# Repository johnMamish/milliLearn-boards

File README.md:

# milliLearn-boards
Dev boards targeting low-power machine learning

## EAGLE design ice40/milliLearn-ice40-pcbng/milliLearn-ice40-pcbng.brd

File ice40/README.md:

#### milliLearn iCE40

milliLearn/iCE40 is an FPGA dev board focused at ultra low-power machine learning research. As a platform itself, it's not meant to be deployed, but is instead meant for benchtop power and performance metering.

The files in the pcb-ng directory are a smaller version of the board that might be less convenient to work with - it saves space at the expense of having limited header pins and no swappable memory modules.

Circuit checklist:
 - [x] 3.3v, 1.8v linear regulators
 - [x] USB port
 - [x] Selectable Vddios
 - [x] FT232H for programming configuration flash
 - [x] iCE40 FPGA
 - [x] configuration flash
 - [x] uart connection from iCE40
 - [x] Connector for [Sparkfun-produced hm01b0 image sensor](https://www.sparkfun.com/products/15570)
 - [x] Modular memory footprints
   - [x] 0.1" header modular pins
      - [x] Swap modules easily
      - [x] Program modules easily
   - [x] 4 spaces for memory chips in total (excluding configuration flash)
   - [x] Choose between the follwing parts, which are all footprint compatible
      - [x] SPI FRAM
      - [x] QSPI Flash
      - [ ] SRAM
 - [x] Current sense amps with header pins for monitoring output voltage
 - [x] Seperate power consumption monitoring for
   - [x] Each memory chip
   - [x] Each sensor
   - [x] FPGA
      - [x] Vddcore + Vddpll
      - [x] Vccio{0, 1, 2}
 - [x] i2s microphone(s)   SPH0645LM4H-B
 - [x] Sparkfun qwiic connect compatible connector
 - [x] All i/os broken out for debug
 - [x] oscillator
 - [x] a couple LEDs, a couple buttons (could re-use config flash pins, hm01b0_int, hm01b0_trig, or ice40_gpio)

Future featues:
 - [ ] Onboard mcu for measuring power in firmware and reporting over UART

random notes:

###### Config memory read speed

When using iceprog, the config flash memory is written by the ft232hq at 6MHz.
The iCE40 starts by reading the config flash at about 12MHz. This is the default read frequency. There are options to put a "speed up the read" near the beginning of the bitstream (refer to Lattice Technical Note 1248: "iCE40 Programming and Configuration")

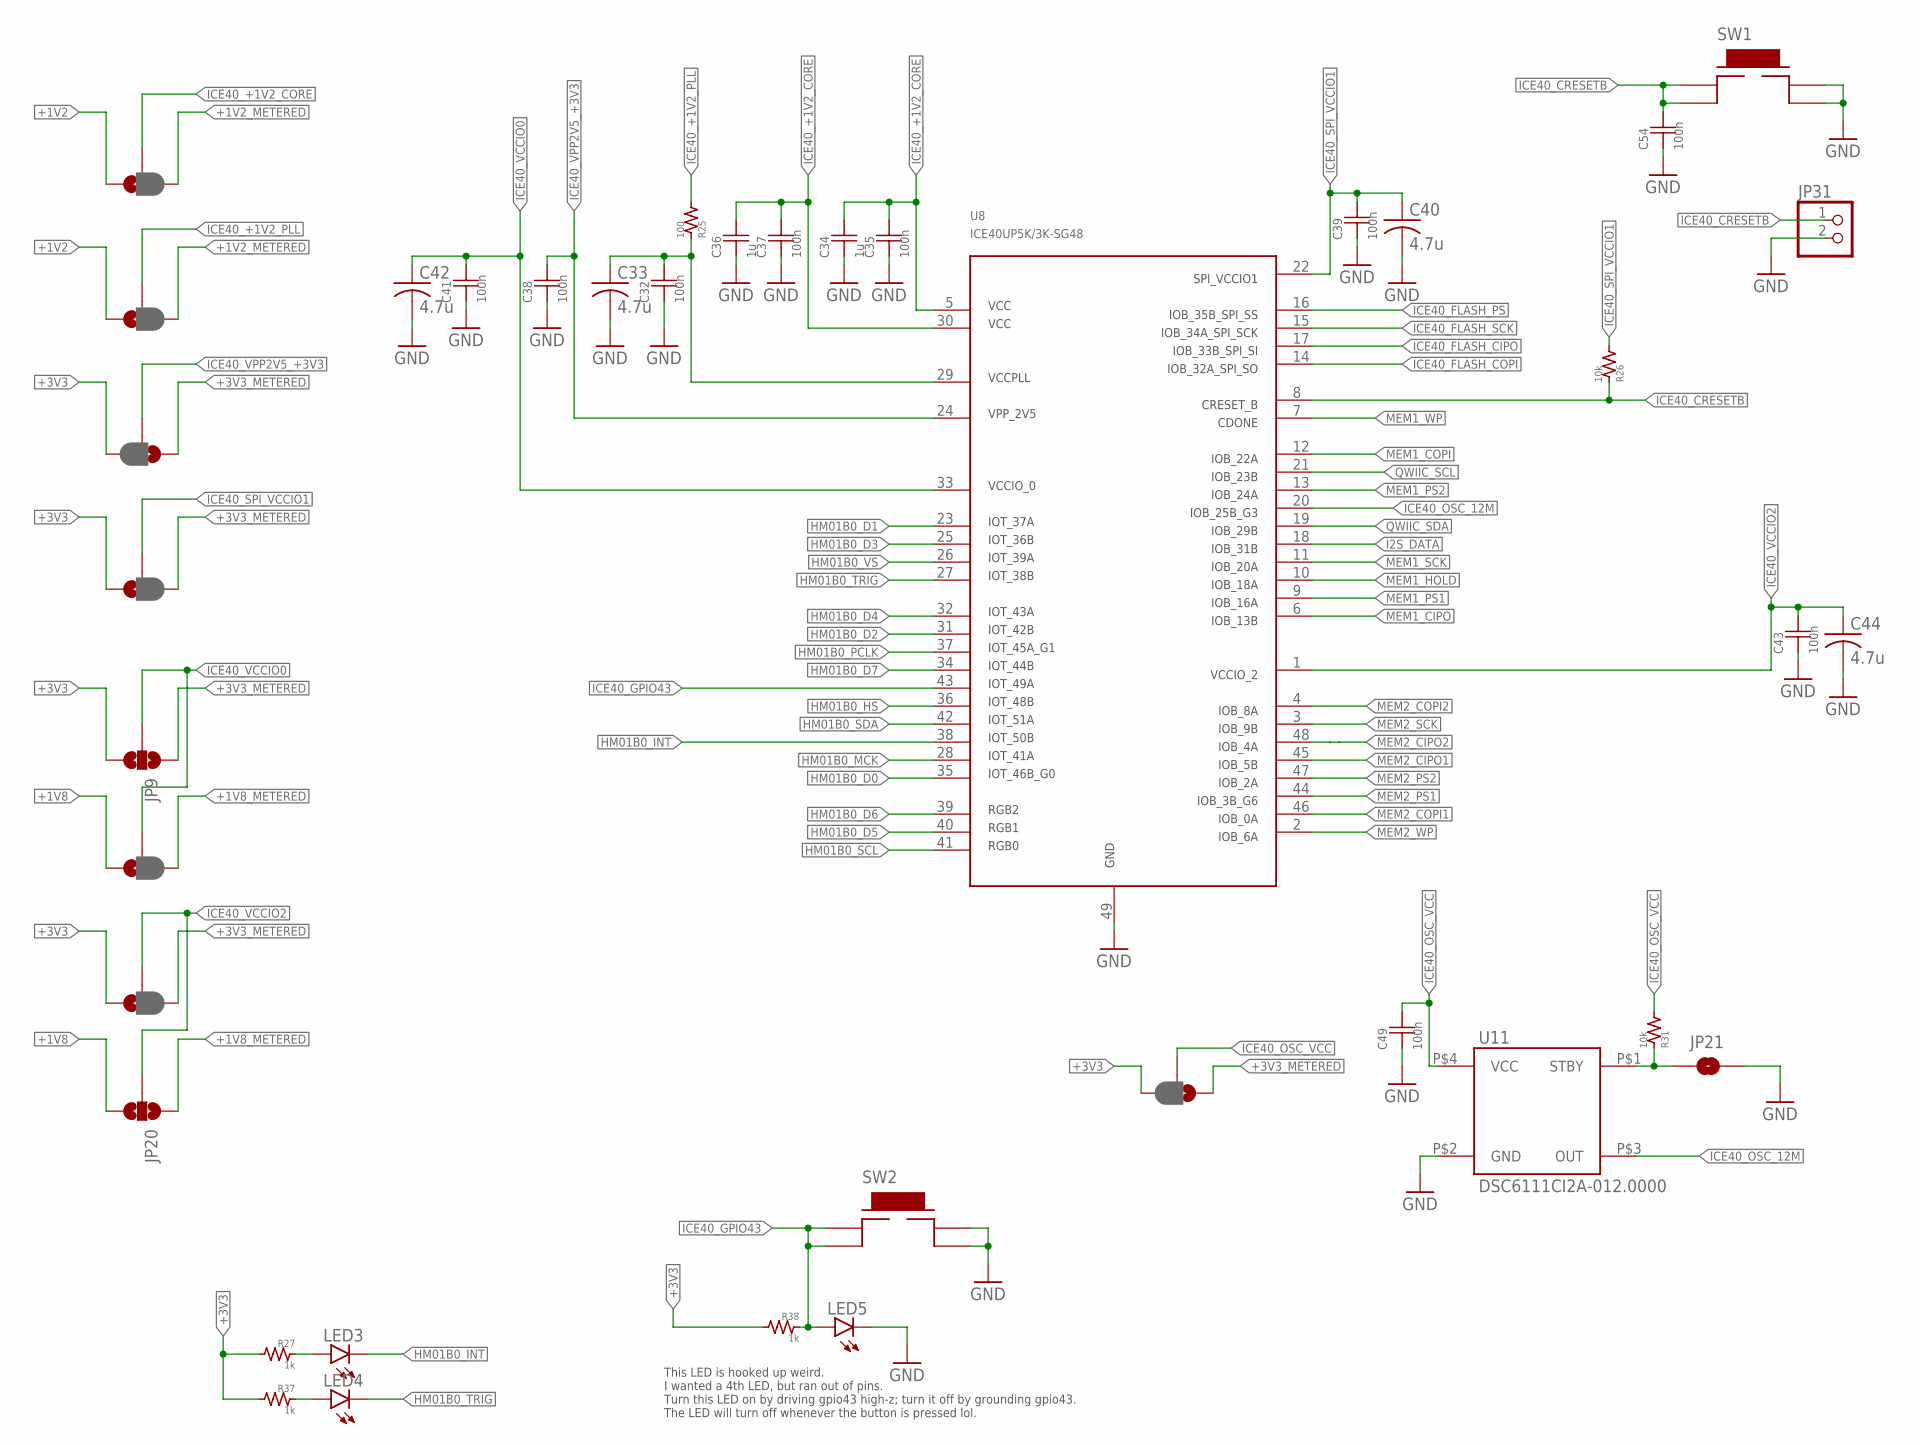
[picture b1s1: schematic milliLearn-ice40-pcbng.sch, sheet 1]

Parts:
C32, C35, C37, C38, C39, C41, C43, C49, C54: 100n; C0402_COMPACT; MFR_PN CL05B104KO5NNNC
C33, C40, C42, C44: 4.7u; C0603; MFR_PN CL10A475KA8NQNC
C34, C36: 1u; C0402_COMPACT; MFR_PN CL05A105KO5NNNC
JP5, JP6, JP7, JP8, JP13, JP14, JP19: JUMPER-SMT_3_1-NC_PASTE_NO-SILK; SMT-JUMPER_3_1-NC_PASTE_NO-SILK
JP9, JP20: JUMPER-SMT_3_NO_NO-SILK; SMT-JUMPER_3_NO_NO-SILK
JP21: JUMPER-SMT_2_NO_NO-SILK; SMT-JUMPER_2_NO_NO-SILK
JP31: PINHD-1X2; 1X02
LED3, LED4, LED5: LEDCHIPLED_0603; CHIPLED_0603; MFR_PN LTST-C191KRKT
R25: 100; R0402_COMPACT; MFR_PN RC0402FR-07100RL
R26, R31: 10k; R0402_COMPACT; MFR_PN ERJ-2RKF1002X
R27, R37, R38: 1k; R0402_COMPACT; MFR_PN ERJ-2RKF1001X
SW1, SW2: TE_FSMJSMA; MFR_PN FSM4JSMATR
U8: ICE40UP5K/3K-SG48; MFR_PN ICE40UP5K-SG48I
U11: DSC6111CI2A-012.0000; MFR_PN DSC6111CI2A-012.0000

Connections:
+1V2: JP5.1, JP6.1; also elsewhere on the board
+1V2_METERED: JP5.3, JP6.3; also elsewhere on the board
+1V8: JP13.1, JP20.3; also elsewhere on the board
+1V8_METERED: JP13.3, JP20.1; also elsewhere on the board
+3V3: JP7.3, JP8.1, JP9.3, JP14.1, JP19.3, R27.1, R37.1, R38.1; also elsewhere on the board
+3V3_METERED: JP7.1, JP8.3, JP9.1, JP14.3, JP19.1; also elsewhere on the board
GND: C32.1, C33.2, C34.1, C35.1, C36.1, C37.1, C38.1, C39.1, C40.2, C41.1, C42.2, C43.1, C44.2, C49.1, C54.1, JP21.2, JP31.2, LED5.C, SW1.P$3, SW1.P$4, SW2.P$3, SW2.P$4, U8.49, U11.P$2 (GND); also elsewhere on the board
HM01B0_D0: U8.35; also elsewhere on the board
HM01B0_D1: U8.23; also elsewhere on the board
HM01B0_D2: U8.31; also elsewhere on the board
HM01B0_D3: U8.25; also elsewhere on the board
HM01B0_D4: U8.32; also elsewhere on the board
HM01B0_D5: U8.40; also elsewhere on the board
HM01B0_D6: U8.39; also elsewhere on the board
HM01B0_D7: U8.34; also elsewhere on the board
HM01B0_HS: U8.36; also elsewhere on the board
HM01B0_INT: LED3.C, U8.38; also elsewhere on the board
HM01B0_MCK: U8.28; also elsewhere on the board
HM01B0_PCLK: U8.37; also elsewhere on the board
HM01B0_SCL: U8.41; also elsewhere on the board
HM01B0_SDA: U8.42; also elsewhere on the board
HM01B0_TRIG: LED4.C, U8.27; also elsewhere on the board
HM01B0_VS: U8.26; also elsewhere on the board
I2S_DATA: U8.18; also elsewhere on the board
ICE40_+1V2_CORE: C34.2, C35.2, C36.2, C37.2, JP5.2, U8.5, U8.30
ICE40_+1V2_PLL: JP6.2, R25.1
ICE40_CRESETB: C54.2, JP31.1, R26.2, SW1.P$1, SW1.P$2, U8.8; also elsewhere on the board
ICE40_FLASH_CIPO: U8.17; also elsewhere on the board
ICE40_FLASH_COPI: U8.14; also elsewhere on the board
ICE40_FLASH_PS: U8.16; also elsewhere on the board
ICE40_FLASH_SCK: U8.15; also elsewhere on the board
ICE40_GPIO43: LED5.A, R38.2, SW2.P$1, SW2.P$2, U8.43
ICE40_OSC_12M: U8.20, U11.P$3 (OUT); also elsewhere on the board
ICE40_OSC_VCC: C49.2, JP19.2, R31.1, U11.P$4 (VCC)
ICE40_SPI_VCCIO1: C39.2, C40.1, JP8.2, R26.1, U8.22
ICE40_VCCIO0: C41.2, C42.1, JP9.2, JP13.2, U8.33
ICE40_VCCIO2: C43.2, C44.1, JP14.2, JP20.2, U8.1
ICE40_VCCPLL: C32.2, C33.1, R25.2, U8.29
ICE40_VPP2V5_+3V3: C38.2, JP7.2, U8.24
MEM1_!HOLD: U8.10; also elsewhere on the board
MEM1_!WP: U8.7; also elsewhere on the board
MEM1_CIPO: U8.6; also elsewhere on the board
MEM1_COPI: U8.12; also elsewhere on the board
MEM1_PS1: U8.9; also elsewhere on the board
MEM1_PS2: U8.13; also elsewhere on the board
MEM1_SCK: U8.11; also elsewhere on the board
MEM2_!WP: U8.2; also elsewhere on the board
MEM2_CIPO1: U8.45; also elsewhere on the board
MEM2_CIPO2: U8.48; also elsewhere on the board
MEM2_COPI1: U8.46; also elsewhere on the board
MEM2_COPI2: U8.4; also elsewhere on the board
MEM2_PS1: U8.44; also elsewhere on the board
MEM2_PS2: U8.47; also elsewhere on the board
MEM2_SCK: U8.3; also elsewhere on the board
unnamed: JP21.1, R31.2, U11.P$1 (STBY)
unnamed: LED3.A, R27.2
unnamed: LED4.A, R37.2
QWIIC_SCL: U8.21; also elsewhere on the board
QWIIC_SDA: U8.19; also elsewhere on the board

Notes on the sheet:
This LED is hooked up weird. I wanted a 4th LED, but ran out of pins. Turn this LED on by driving gpio43 high-z; turn it off by grounding gpio43. The LED will turn off whenever the button is pressed lol.

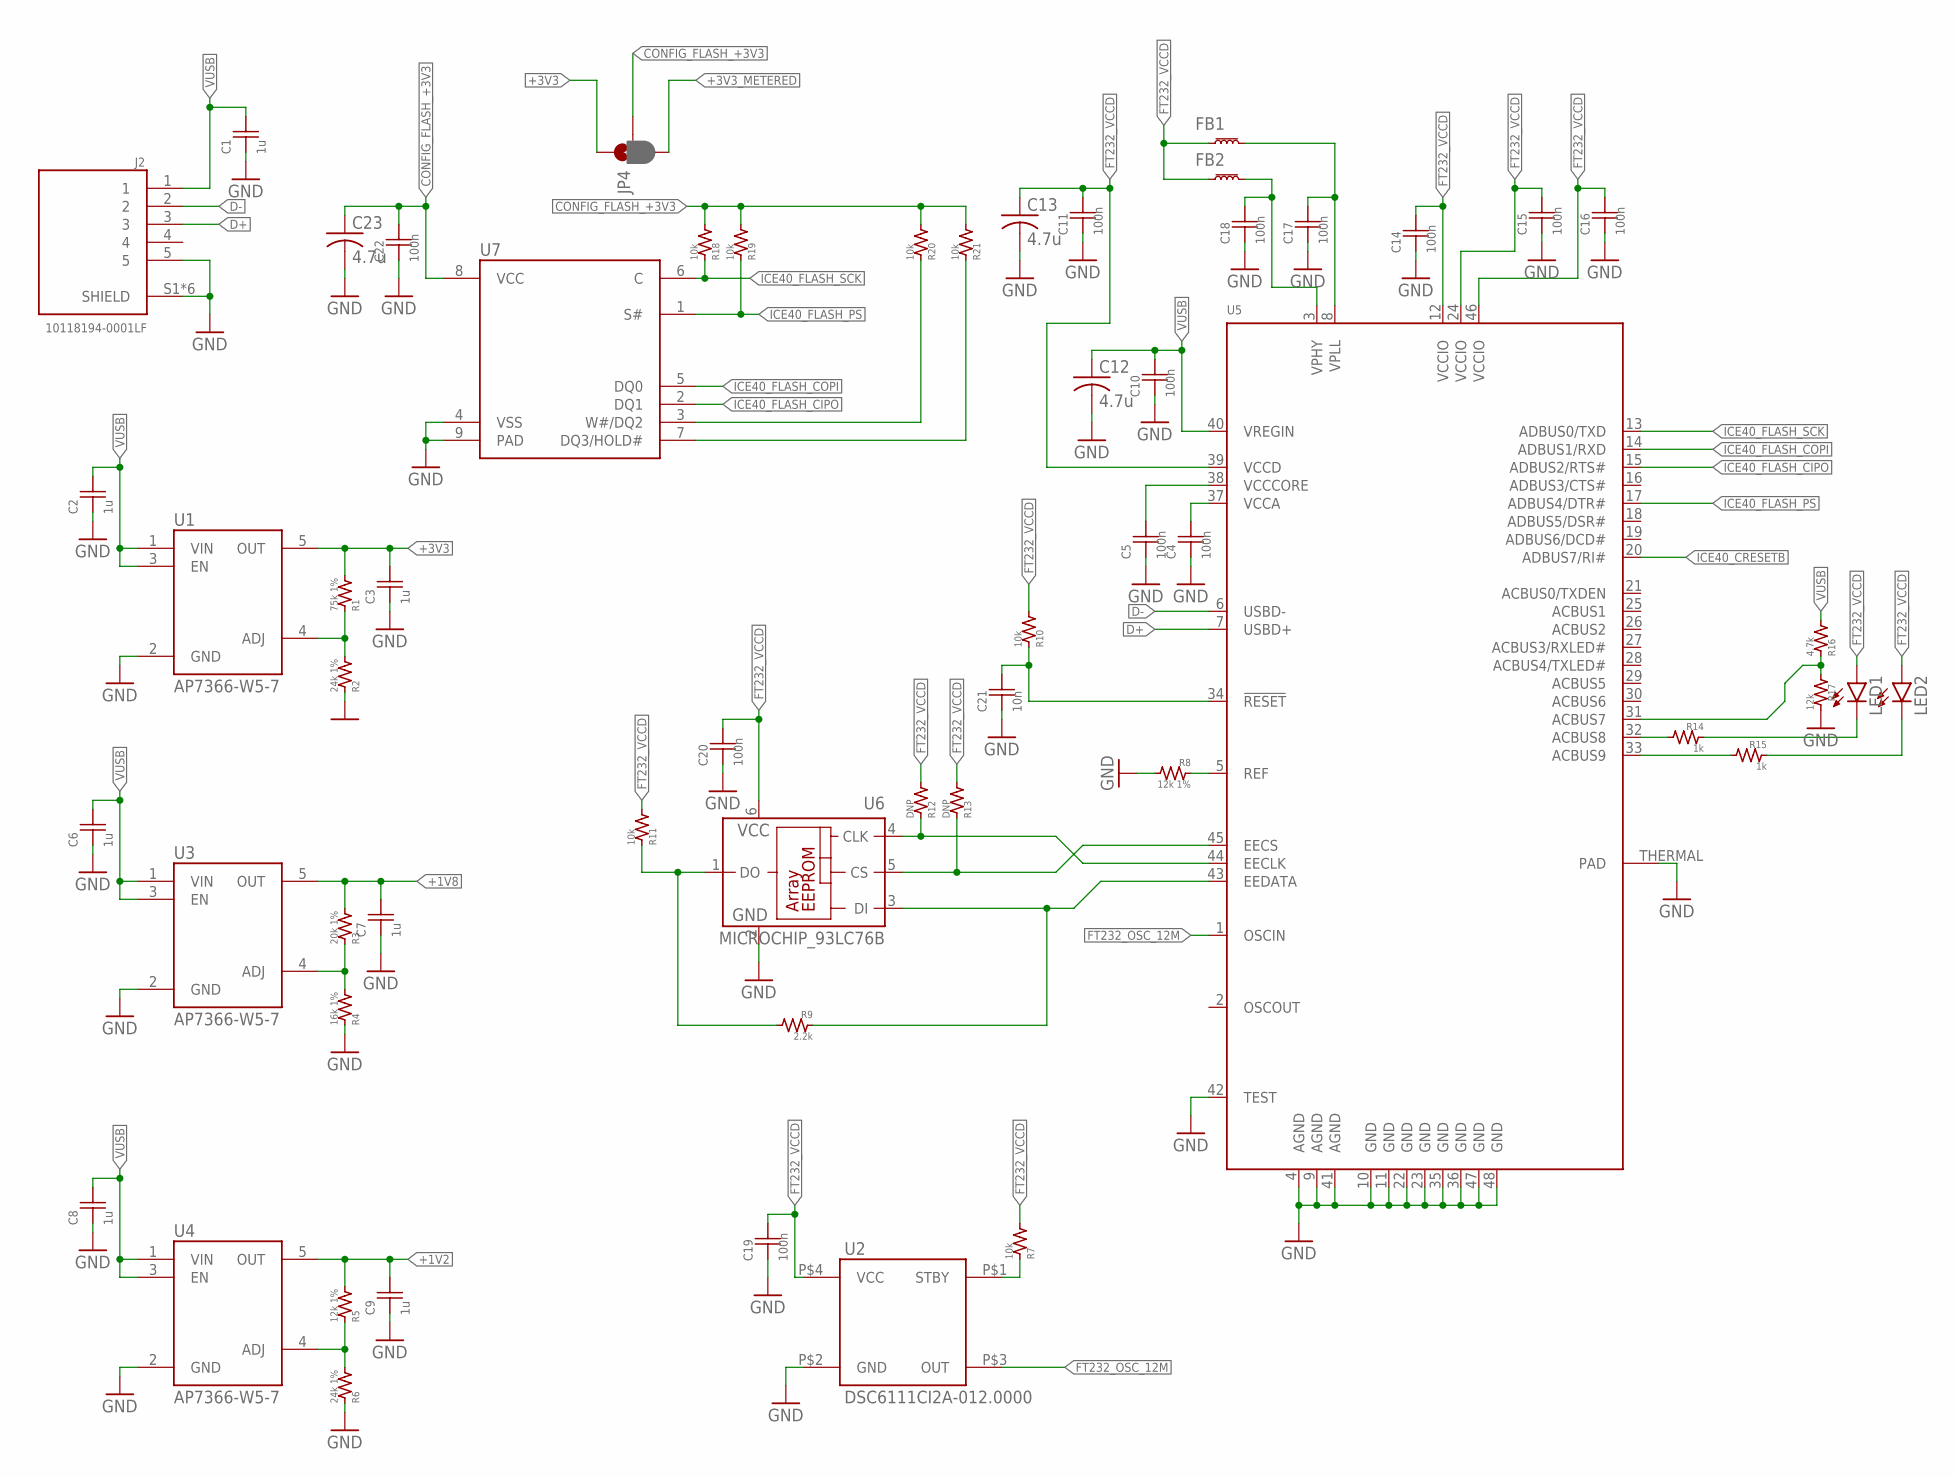
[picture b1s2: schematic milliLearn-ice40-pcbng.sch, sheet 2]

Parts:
C1, C2, C3, C6, C7, C8, C9: 1u; C0402_COMPACT; MFR_PN CL05A105KO5NNNC
C4, C5, C10, C11, C14, C15, C16, C17, C18, C19, C20, C22: 100n; C0402_COMPACT; MFR_PN CL05B104KO5NNNC
C12, C13, C23: 4.7u; C0603; MFR_PN CL10A475KA8NQNC
C21: 10n; C0402_COMPACT; MFR_PN CL05B103KO5NNNC
FB1, FB2: BLM18KG601SN1D
J2: 10118194-0001LF; AMPHENOL_10118194-0001LF; MFR_PN 10118194-0001LF
JP4: JUMPER-SMT_3_1-NC_PASTE_NO-SILK; SMT-JUMPER_3_1-NC_PASTE_NO-SILK
LED1, LED2: LEDCHIPLED_0603; CHIPLED_0603; MFR_PN LTST-C191KRKT
R1: 75k 1%; R0402_COMPACT; MFR_PN ERJ-2RKF7502X
R2, R6: 24k 1%; R0402_COMPACT; MFR_PN ERJ-2RKF2402X
R3: 20k 1%; R0402_COMPACT; MFR_PN ERJ-2RKF2002X
R4: 16k 1%; R0402_COMPACT; MFR_PN ERJ-2RKF1602X
R5, R8: 12k 1%; R0402_COMPACT; MFR_PN ERJ-2RKF1202X
R7, R10, R11, R18, R19, R20, R21: 10k; R0402_COMPACT; MFR_PN ERJ-2RKF1002X
R9: 2.2k; R0402_COMPACT; MFR_PN ERJ-2RKF2201X
R12, R13: DNP; R0402_COMPACT; MFR_PN ERJ-2RKF1002X
R14, R15: 1k; R0402_COMPACT; MFR_PN ERJ-2RKF1001X
R16: 4.7k; R0402_COMPACT; MFR_PN ERJ-2RKF4701X
R17: 12k; R0402_COMPACT; MFR_PN ERJ-2RKF1202X
U1, U3, U4: AP7366-W5-7
U2: DSC6111CI2A-012.0000; MFR_PN DSC6111CI2A-012.0000
U5: MICROBUILDER_FT232HQ; MICROBUILDER_QFN48_8MM; MFR_PN FT232HQ-REEL
U6: MICROCHIP_93LC76B; MICROCHIP_SOT23-6; MFR_PN 93LC56BT-I/OT
U7: MT25QL128ABA1EW7; MFR_PN MT25QL128ABA1EW7-0SIT

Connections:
+1V2: C9.2, R5.1, U4.5 (OUT); also elsewhere on the board
+1V8: C7.2, R3.1, U3.5 (OUT); also elsewhere on the board
+3V3: C3.2, JP4.1, R1.1, U1.5 (OUT); also elsewhere on the board
+3V3_METERED: JP4.3; also elsewhere on the board
CONFIG_FLASH_+3V3: C22.2, C23.1, JP4.2, R18.1, R19.1, R20.1, R21.1, U7.8 (VCC)
D+: J2.3, U5.7 (USBD+)
D-: J2.2, U5.6 (USBD-)
FT232_OSC_12M: U2.P$3 (OUT), U5.1 (OSCIN)
FT232_VCCD: C11.2, C13.1, C14.2, C15.2, C16.2, C19.2, C20.2, FB1.1, FB2.1, LED1.A, LED2.A, R7.1, R10.1, R11.1, R12.1, R13.1, U2.P$4 (VCC), U5.12 (VCCIO), U5.24 (VCCIO), U5.39 (VCCD), U5.46 (VCCIO), U6.6 (VCC)
GND: C1.1, C2.1, C3.1, C4.1, C5.1, C6.1, C7.1, C8.1, C9.1, C10.1, C11.1, C12.2, C13.2, C14.1, C15.1, C16.1, C17.1, C18.1, C19.1, C20.1, C21.1, C22.1, C23.2, J2.5, J2.S1 (SHIELD), J2.S2 (SHIELD), J2.S3 (SHIELD), J2.S4 (SHIELD), J2.S5 (SHIELD), J2.S6 (SHIELD), R2.2, R4.2, R6.2, R8.1, R17.2, U1.2 (GND), U2.P$2 (GND), U3.2 (GND), U4.2 (GND), U5.4 (AGND), U5.9 (AGND), U5.10 (GND), U5.11 (GND), U5.22 (GND), U5.23 (GND), U5.35 (GND), U5.36 (GND), U5.41 (AGND), U5.42 (TEST), U5.47 (GND), U5.48 (GND), U5.THERMAL (PAD), U6.2 (GND), U7.4 (VSS), U7.9 (PAD); also elsewhere on the board
ICE40_CRESETB: U5.20 (ADBUS7/RI#); also elsewhere on the board
ICE40_FLASH_CIPO: U5.15 (ADBUS2/RTS#), U7.2 (DQ1); also elsewhere on the board
ICE40_FLASH_COPI: U5.14 (ADBUS1/RXD), U7.5 (DQ0); also elsewhere on the board
ICE40_FLASH_PS: R19.2, U5.17 (ADBUS4/DTR#), U7.1 (S#); also elsewhere on the board
ICE40_FLASH_SCK: R18.2, U5.13 (ADBUS0/TXD), U7.6 (C); also elsewhere on the board
unnamed: R5.2, R6.1, U4.4 (ADJ)
unnamed: R1.2, R2.1, U1.4 (ADJ)
unnamed: C18.2, FB2.2, U5.3 (VPHY)
unnamed: C17.2, FB1.2, U5.8 (VPLL)
unnamed: R3.2, R4.1, U3.4 (ADJ)
unnamed: R7.2, U2.P$1 (STBY)
unnamed: R9.1, R11.2, U6.1 (DO)
unnamed: R8.2, U5.5 (REF)
unnamed: R9.2, U5.43 (EEDATA), U6.3 (DI)
unnamed: R13.2, U5.45 (EECS), U6.5 (CS)
unnamed: R12.2, U5.44 (EECLK), U6.4 (CLK)
unnamed: R14.1, U5.32 (ACBUS8)
unnamed: C21.2, R10.2, U5.34 (!RESET)
unnamed: LED1.C, R14.2
unnamed: R16.2, R17.1, U5.31 (ACBUS7)
unnamed: R15.1, U5.33 (ACBUS9)
unnamed: LED2.C, R15.2
unnamed: R20.2, U7.3 (W#/DQ2)
unnamed: R21.2, U7.7 (DQ3/HOLD#)
VCCA: C4.2, U5.37 (VCCA)
VCCCORE: C5.2, U5.38 (VCCCORE)
VUSB: C1.2, C2.2, C6.2, C8.2, C10.2, C12.1, J2.1, R16.1, U1.1 (VIN), U1.3 (EN), U3.1 (VIN), U3.3 (EN), U4.1 (VIN), U4.3 (EN), U5.40 (VREGIN); also elsewhere on the board

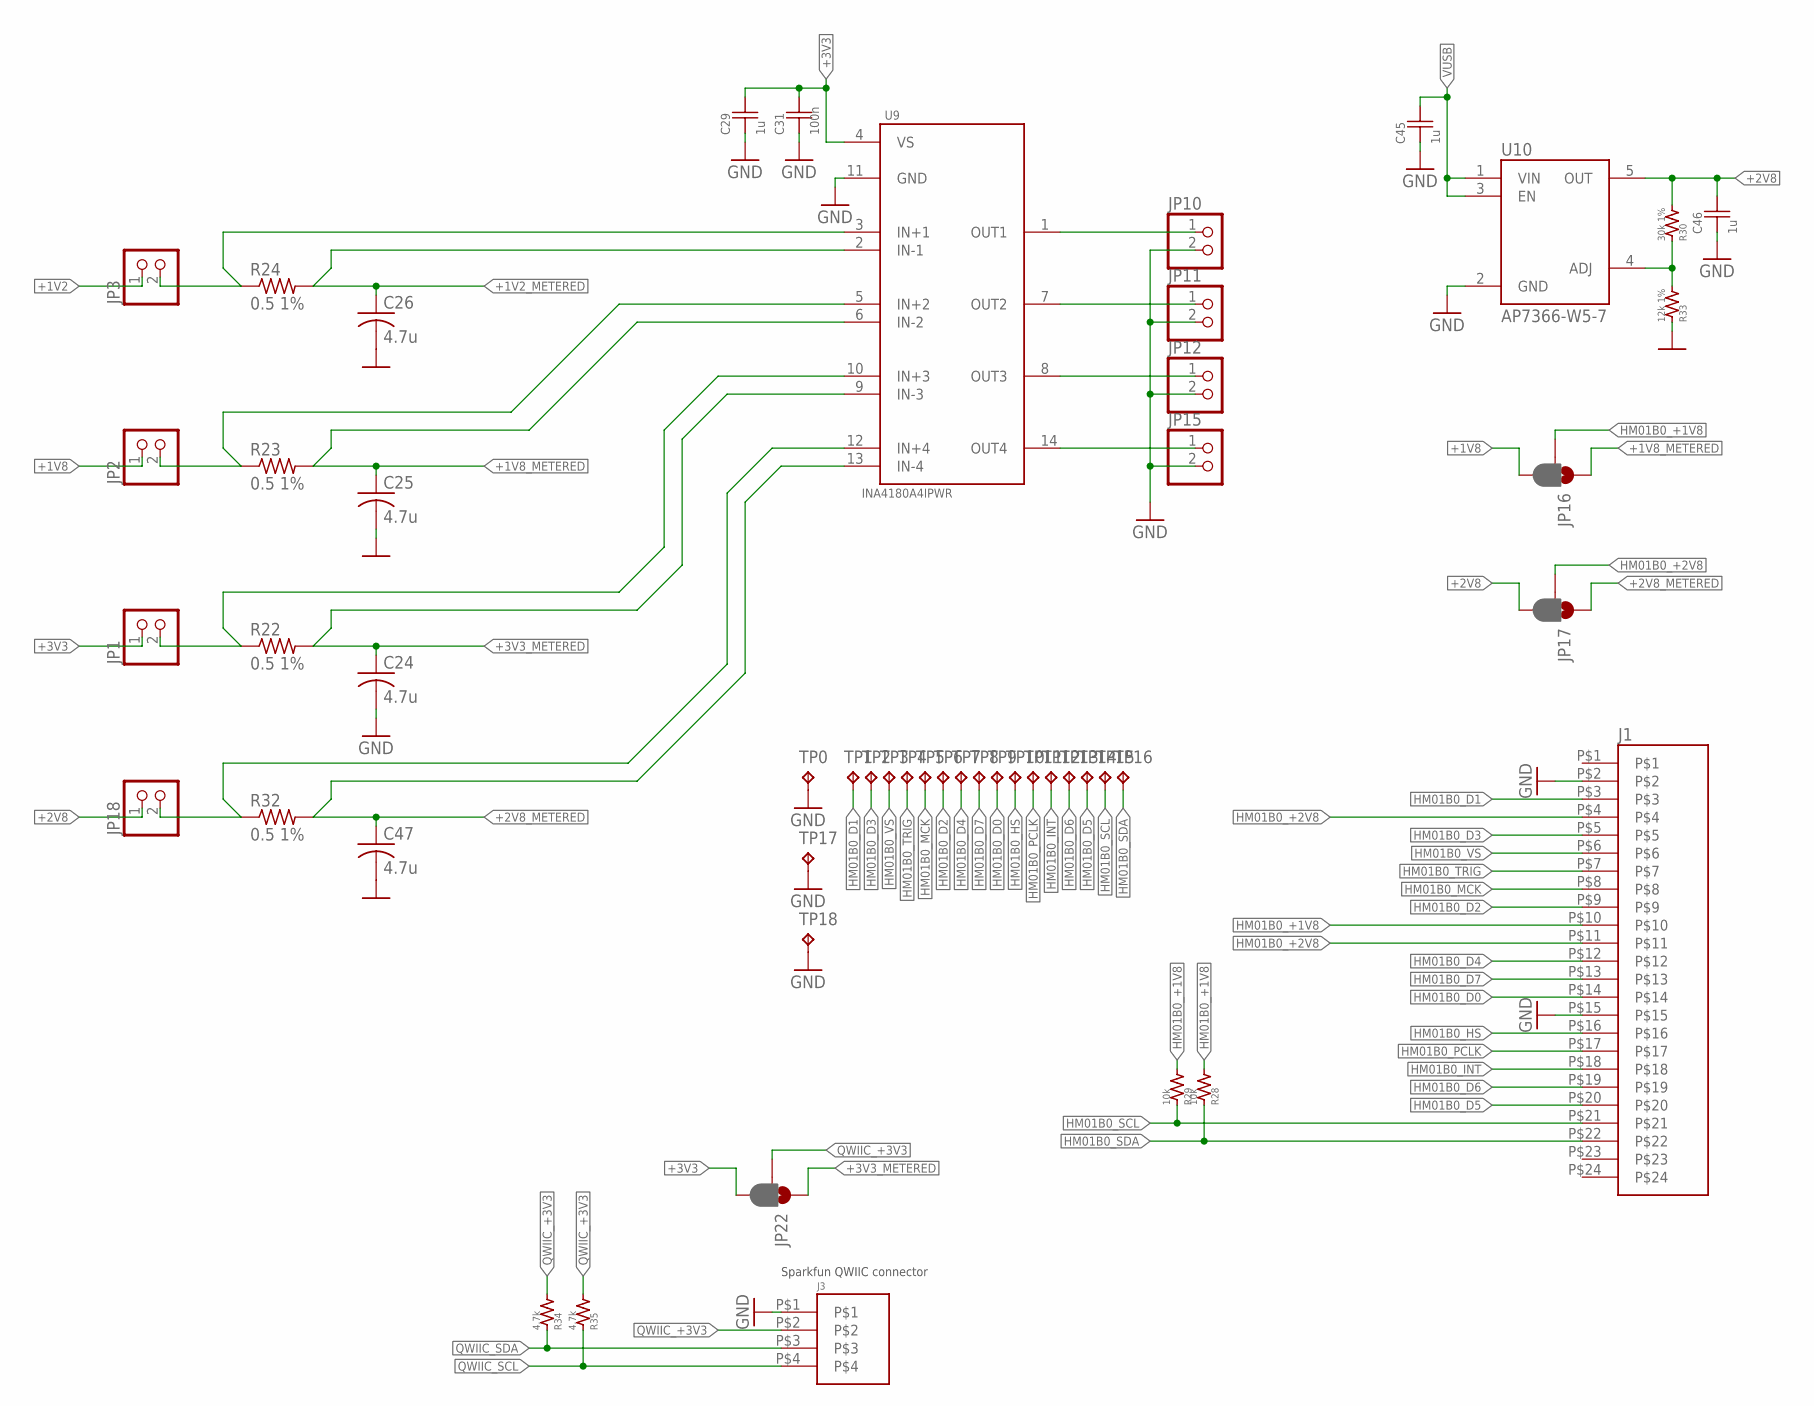
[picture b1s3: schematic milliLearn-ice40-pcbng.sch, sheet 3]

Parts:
C24, C25, C26, C47: 4.7u; C0603; MFR_PN CL10A475KA8NQNC
C29, C45, C46: 1u; C0402_COMPACT; MFR_PN CL05A105KO5NNNC
C31: 100n; C0402_COMPACT; MFR_PN CL05B104KO5NNNC
J1: SFV24R-2STE1HLF; MFR_PN SFV24R-2STE1HLF
J3: SM04B-SRSS-TB(LF)(SN); MFR_PN SM04B-SRSS-TB(LF)(SN)
JP1, JP2, JP3, JP10, JP11, JP12, JP15, JP18: PINHD-1X2; 1X02; MFR_PN 61300211121
JP16, JP17, JP22: JUMPER-SMT_3_1-NC_PASTE_NO-SILK; SMT-JUMPER_3_1-NC_PASTE_NO-SILK
R22, R23, R24, R32: 0.5 1%; R0603; MFR_PN RL0603FR-070R5L
R28, R29: 10k; R0402_COMPACT; MFR_PN ERJ-2RKF1002X
R30: 30k 1%; R0402_COMPACT; MFR_PN ERJ-2RKF3002X
R33: 12k 1%; R0402_COMPACT; MFR_PN ERJ-2RKF1202X
R34, R35: 4.7k; R0402_COMPACT; MFR_PN ERJ-2RKF4701X
TP0, TP1, TP2, TP3, TP4, TP5, TP6, TP7, TP8, TP9, TP10, TP11, TP12, TP13, TP14, TP15, TP16, TP17, TP18: TPTP10SQ; TP10SQ
U9: INA4180A4IPWR
U10: AP7366-W5-7

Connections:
+1V2: JP3.1; also elsewhere on the board
+1V2_METERED: C26.1, R24.2, U9.2 (IN-1); also elsewhere on the board
+1V8: JP2.1, JP16.3; also elsewhere on the board
+1V8_METERED: C25.1, JP16.1, R23.2, U9.6 (IN-2); also elsewhere on the board
+2V8: C46.2, JP17.3, JP18.1, R30.1, U10.5 (OUT)
+2V8_METERED: C47.1, JP17.1, R32.2, U9.13 (IN-4)
+3V3: C29.2, C31.2, JP1.1, JP22.3, U9.4 (VS); also elsewhere on the board
+3V3_METERED: C24.1, JP22.1, R22.2, U9.9 (IN-3); also elsewhere on the board
GND: C24.2, C25.2, C26.2, C29.1, C31.1, C45.1, C46.1, C47.2, J1.P$2, J1.P$15, J3.P$1, JP10.2, JP11.2, JP12.2, JP15.2, R33.2, TP0.TP, TP17.TP, TP18.TP, U9.11 (GND), U10.2 (GND); also elsewhere on the board
HM01B0_+1V8: J1.P$10, JP16.2, R28.1, R29.1
HM01B0_+2V8: J1.P$4, J1.P$11, JP17.2
HM01B0_D0: J1.P$14, TP9.TP; also elsewhere on the board
HM01B0_D1: J1.P$3, TP1.TP; also elsewhere on the board
HM01B0_D2: J1.P$9, TP6.TP; also elsewhere on the board
HM01B0_D3: J1.P$5, TP2.TP; also elsewhere on the board
HM01B0_D4: J1.P$12, TP7.TP; also elsewhere on the board
HM01B0_D5: J1.P$20, TP14.TP; also elsewhere on the board
HM01B0_D6: J1.P$19, TP13.TP; also elsewhere on the board
HM01B0_D7: J1.P$13, TP8.TP; also elsewhere on the board
HM01B0_HS: J1.P$16, TP10.TP; also elsewhere on the board
HM01B0_INT: J1.P$18, TP12.TP; also elsewhere on the board
HM01B0_MCK: J1.P$8, TP5.TP; also elsewhere on the board
HM01B0_PCLK: J1.P$17, TP11.TP; also elsewhere on the board
HM01B0_SCL: J1.P$21, R29.2, TP15.TP; also elsewhere on the board
HM01B0_SDA: J1.P$22, R28.2, TP16.TP; also elsewhere on the board
HM01B0_TRIG: J1.P$7, TP4.TP; also elsewhere on the board
HM01B0_VS: J1.P$6, TP3.TP; also elsewhere on the board
MEAS_1V2: JP10.1, U9.1 (OUT1)
MEAS_1V8: JP11.1, U9.7 (OUT2)
MEAS_2V8: JP15.1, U9.14 (OUT4)
MEAS_3V3: JP12.1, U9.8 (OUT3)
unnamed: JP3.2, R24.1, U9.3 (IN+1)
unnamed: JP2.2, R23.1, U9.5 (IN+2)
unnamed: JP1.2, R22.1, U9.10 (IN+3)
unnamed: R30.2, R33.1, U10.4 (ADJ)
unnamed: JP18.2, R32.1, U9.12 (IN+4)
QWIIC_+3V3: J3.P$2, JP22.2, R34.1, R35.1
QWIIC_SCL: J3.P$4, R35.2; also elsewhere on the board
QWIIC_SDA: J3.P$3, R34.2; also elsewhere on the board
VUSB: C45.2, U10.1 (VIN), U10.3 (EN); also elsewhere on the board

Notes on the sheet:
Sparkfun QWIIC connector

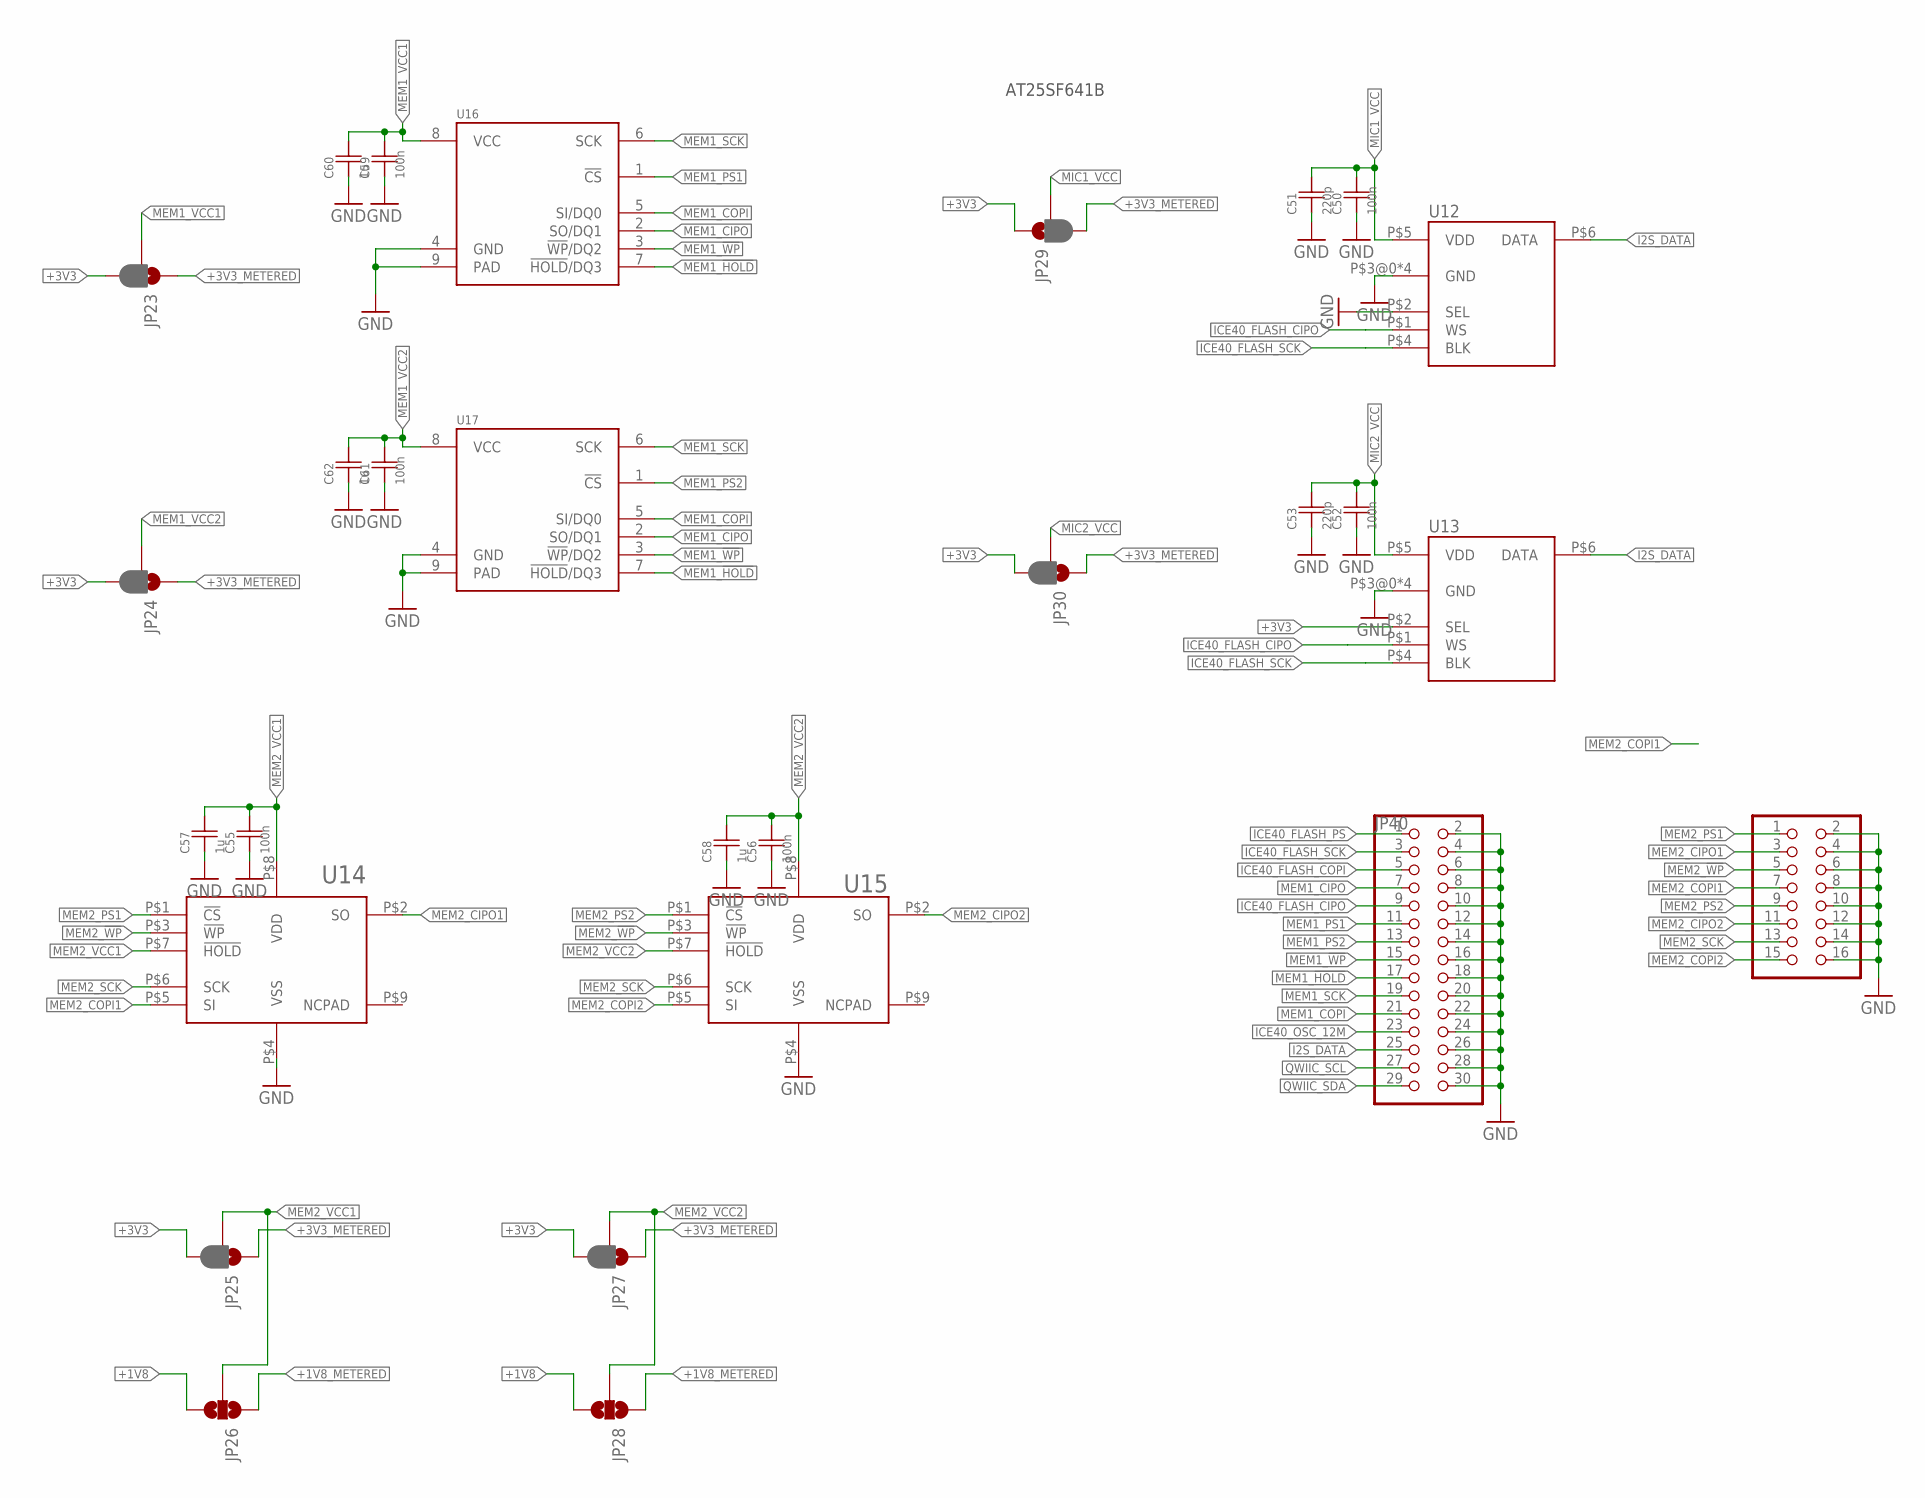
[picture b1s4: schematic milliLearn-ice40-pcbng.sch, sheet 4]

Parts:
C50, C52, C55, C56, C59, C61: 100n; C0402_COMPACT; MFR_PN CL05B104KO5NNNC
C51, C53: 220p; C0402_COMPACT; MFR_PN CL05B221KB5NNNC
C57, C58, C60, C62: 1u; C0402_COMPACT; MFR_PN CL05A105KO5NNNC
JP23, JP24, JP25, JP27, JP29, JP30: JUMPER-SMT_3_1-NC_PASTE_NO-SILK; SMT-JUMPER_3_1-NC_PASTE_NO-SILK
JP26, JP28: JUMPER-SMT_3_NO_NO-SILK; SMT-JUMPER_3_NO_NO-SILK
JP40: PINHD-2X15; 2X15
JP41: PINHD-2X8; 2X08
U12, U13: SPH0645LM4H-B
U14, U15: CY15B104Q-LHXI; MFR_PN CY15B104Q-LHXI
U16, U17: AT25QF641B-SHB-T; MFR_PN AT25QF641B-SHB-T

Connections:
+1V8: JP26.3, JP28.3; also elsewhere on the board
+1V8_METERED: JP26.1, JP28.1; also elsewhere on the board
+3V3: JP23.3, JP24.3, JP25.3, JP27.3, JP29.1, JP30.3, U13.P$2 (SEL); also elsewhere on the board
+3V3_METERED: JP23.1, JP24.1, JP25.1, JP27.1, JP29.3, JP30.1; also elsewhere on the board
GND: C50.1, C51.1, C52.1, C53.1, C55.1, C56.1, C57.1, C58.1, C59.1, C60.1, C61.1, C62.1, JP40.2, JP40.4, JP40.6, JP40.8, JP40.10, JP40.12, JP40.14, JP40.16, JP40.18, JP40.20, JP40.22, JP40.24, JP40.26, JP40.28, JP40.30, JP41.2, JP41.4, JP41.6, JP41.8, JP41.10, JP41.12, JP41.14, JP41.16, U12.P$2 (SEL), U12.P$3@0 (GND), U12.P$3@1 (GND), U12.P$3@2 (GND), U12.P$3@3 (GND), U13.P$3@0 (GND), U13.P$3@1 (GND), U13.P$3@2 (GND), U13.P$3@3 (GND), U14.P$4 (VSS), U15.P$4 (VSS), U16.4 (GND), U16.9 (PAD), U17.4 (GND), U17.9 (PAD); also elsewhere on the board
I2S_DATA: JP40.25, U12.P$6 (DATA), U13.P$6 (DATA); also elsewhere on the board
ICE40_FLASH_CIPO: JP40.9, U12.P$1 (WS), U13.P$1 (WS); also elsewhere on the board
ICE40_FLASH_COPI: JP40.5; also elsewhere on the board
ICE40_FLASH_PS: JP40.1; also elsewhere on the board
ICE40_FLASH_SCK: JP40.3, U12.P$4 (BLK), U13.P$4 (BLK); also elsewhere on the board
ICE40_OSC_12M: JP40.23; also elsewhere on the board
MEM1_!HOLD: JP40.17, U16.7 (!HOLD!/DQ3), U17.7 (!HOLD!/DQ3); also elsewhere on the board
MEM1_!WP: JP40.15, U16.3 (!WP!/DQ2), U17.3 (!WP!/DQ2); also elsewhere on the board
MEM1_CIPO: JP40.7, U16.2 (SO/DQ1), U17.2 (SO/DQ1); also elsewhere on the board
MEM1_COPI: JP40.21, U16.5 (SI/DQ0), U17.5 (SI/DQ0); also elsewhere on the board
MEM1_PS1: JP40.11, U16.1 (!CS); also elsewhere on the board
MEM1_PS2: JP40.13, U17.1 (!CS); also elsewhere on the board
MEM1_SCK: JP40.19, U16.6 (SCK), U17.6 (SCK); also elsewhere on the board
MEM1_VCC1: C59.2, C60.2, JP23.2, U16.8 (VCC)
MEM1_VCC2: C61.2, C62.2, JP24.2, U17.8 (VCC)
MEM2_!WP: JP41.5, U14.P$3 (!WP), U15.P$3 (!WP); also elsewhere on the board
MEM2_CIPO1: JP41.3, U14.P$2 (SO); also elsewhere on the board
MEM2_CIPO2: JP41.11, U15.P$2 (SO); also elsewhere on the board
MEM2_COPI1: JP41.7, U14.P$5 (SI); also elsewhere on the board
MEM2_COPI2: JP41.15, U15.P$5 (SI); also elsewhere on the board
MEM2_PS1: JP41.1, U14.P$1 (!CS); also elsewhere on the board
MEM2_PS2: JP41.9, U15.P$1 (!CS); also elsewhere on the board
MEM2_SCK: JP41.13, U14.P$6 (SCK), U15.P$6 (SCK); also elsewhere on the board
MEM2_VCC1: C55.2, C57.2, JP25.2, JP26.2, U14.P$7 (!HOLD), U14.P$8 (VDD)
MEM2_VCC2: C56.2, C58.2, JP27.2, JP28.2, U15.P$7 (!HOLD), U15.P$8 (VDD)
MIC1_VCC: C50.2, C51.2, JP29.2, U12.P$5 (VDD)
MIC2_VCC: C52.2, C53.2, JP30.2, U13.P$5 (VDD)
QWIIC_SCL: JP40.27; also elsewhere on the board
QWIIC_SDA: JP40.29; also elsewhere on the board

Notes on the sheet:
AT25SF641B

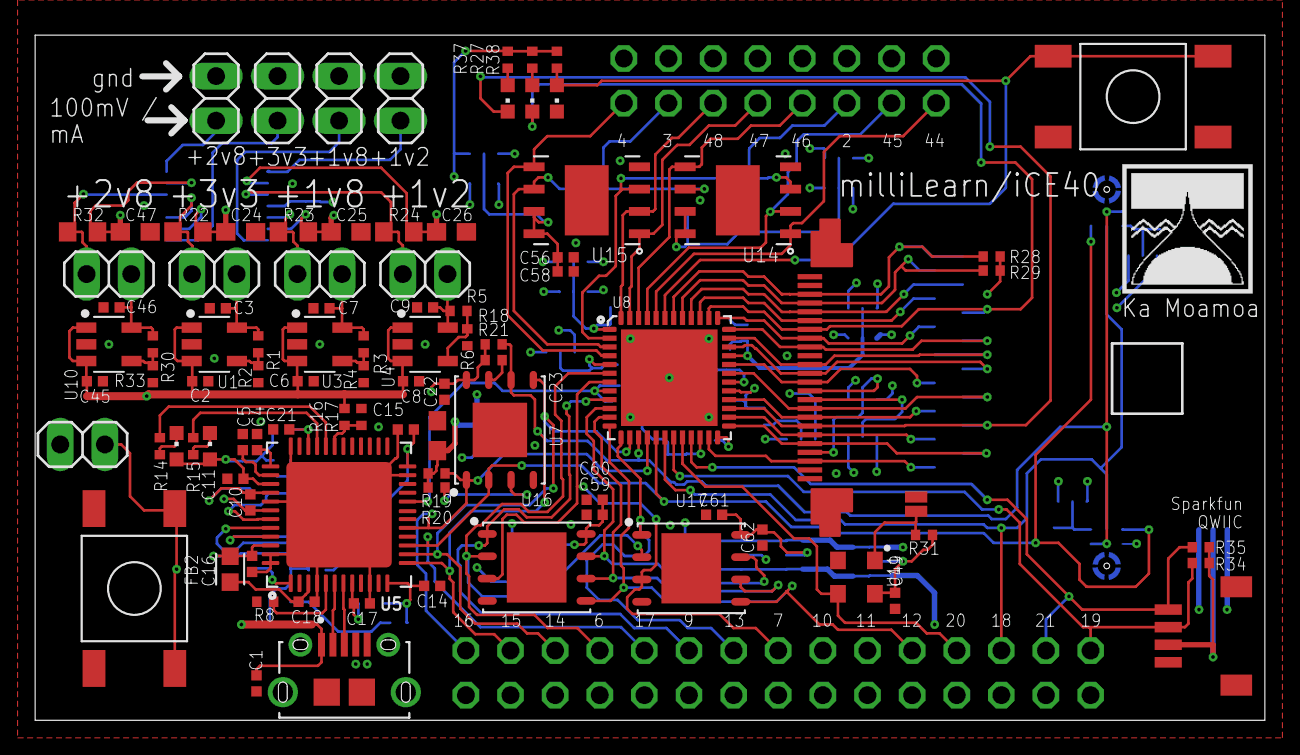
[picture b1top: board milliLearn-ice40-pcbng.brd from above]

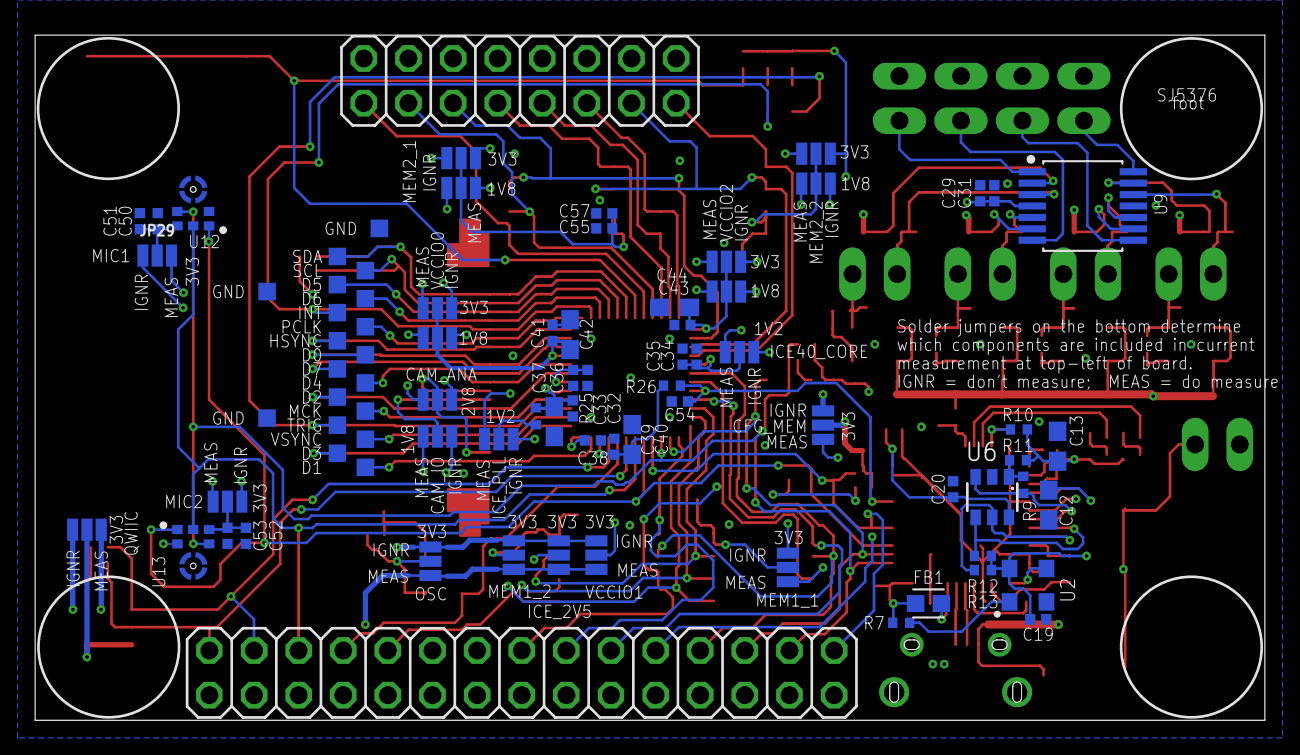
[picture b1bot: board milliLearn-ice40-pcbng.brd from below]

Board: 4 copper layers, 70.0 x 39.0 mm, 176 parts (82 on the bottom side), 106 nets.

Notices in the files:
parts and their libraries:
SparkFun-Jumpers: Licensing: Creative Commons ShareAlike 4.0 International - https://creativecommons.org/licenses/by-sa/4.0
